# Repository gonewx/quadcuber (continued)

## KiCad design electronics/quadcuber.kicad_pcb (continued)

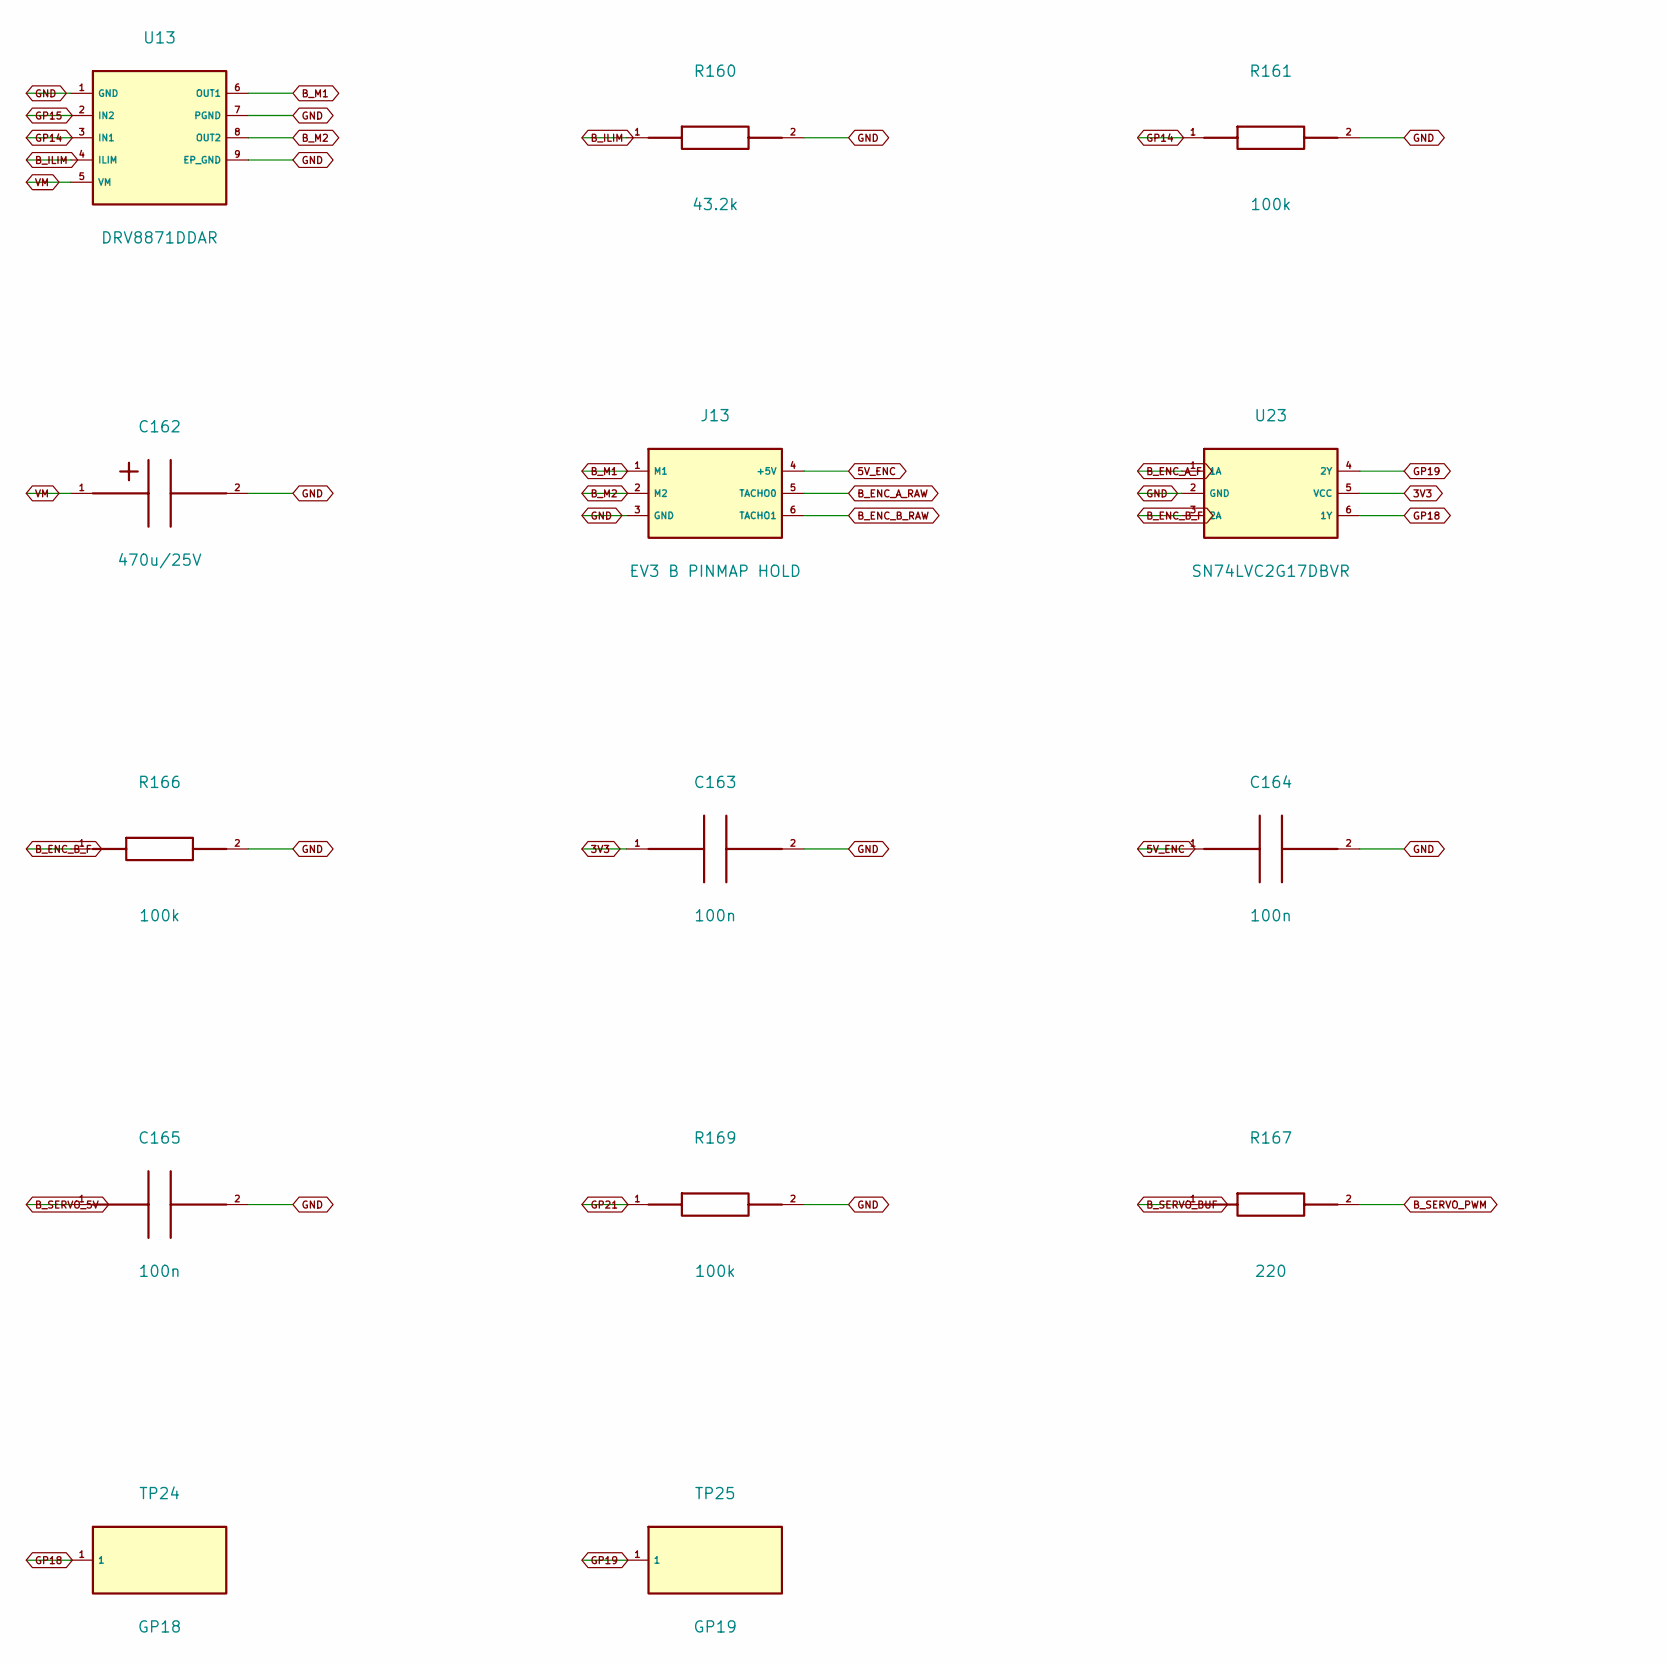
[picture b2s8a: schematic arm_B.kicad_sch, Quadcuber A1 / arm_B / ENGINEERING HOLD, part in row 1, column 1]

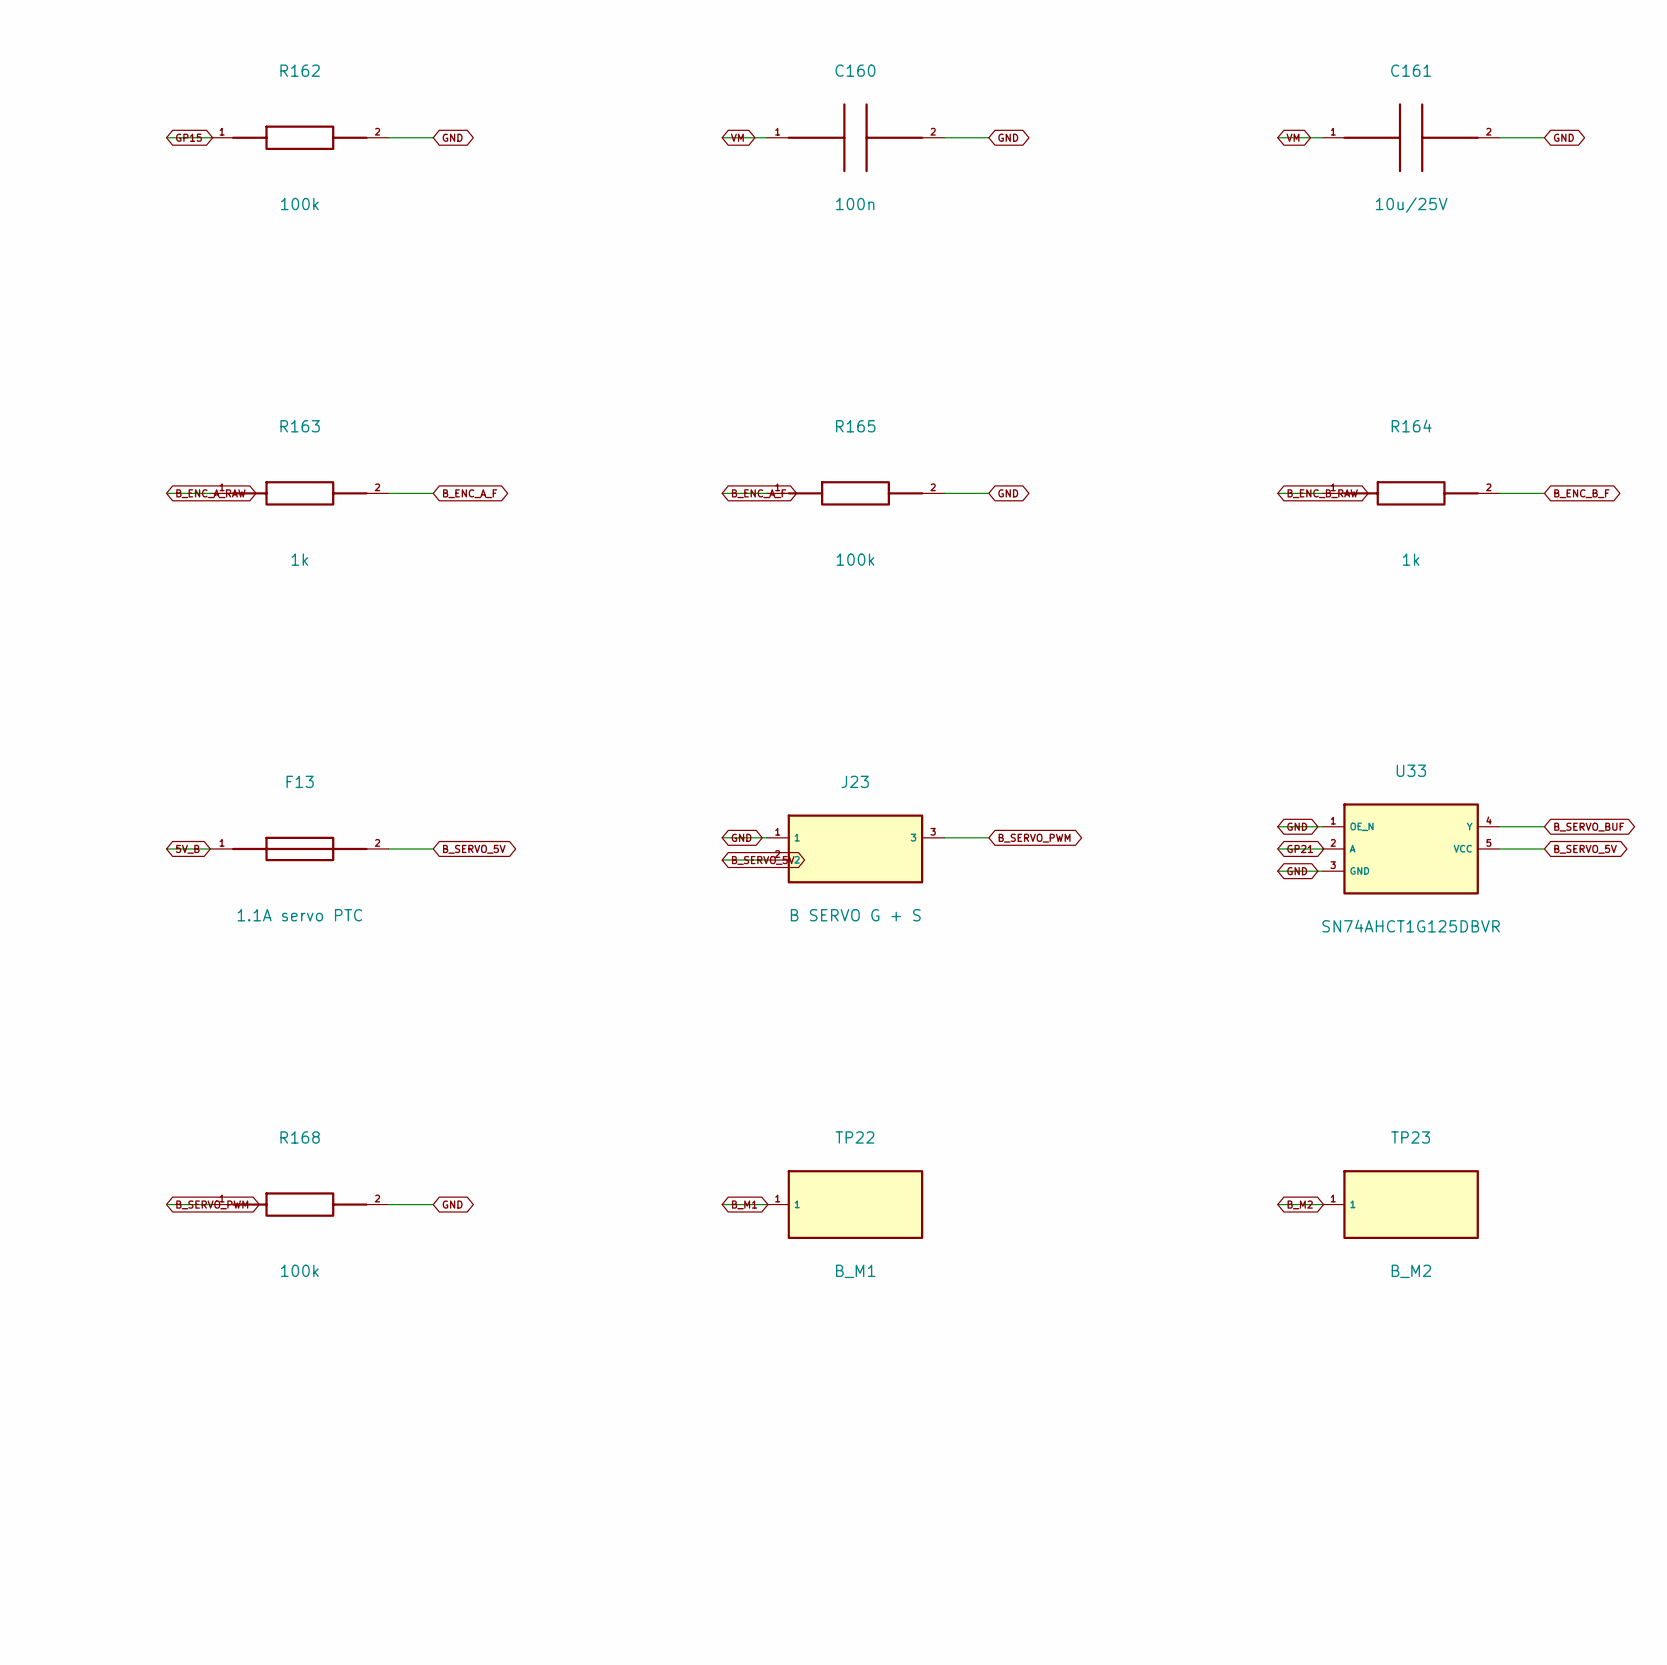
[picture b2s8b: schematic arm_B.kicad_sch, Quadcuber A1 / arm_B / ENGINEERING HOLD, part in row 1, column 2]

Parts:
C160, C163, C164, C165: 100n; C_0805_2012Metric; MPN GRM21BR71H104KA01L
C161: 10u/25V; C_1210_3225Metric; MPN GRM32DR71E106KA12L
C162: 470u/25V; CP_Radial_D10.0mm_P5.00mm; MPN EEU-FR1E471
F13: 1.1A servo PTC; Fuse_Bourns_MF_MSMF_Style2_1812; MPN MF-MSMF110/16X-2
J13: EV3 B PINMAP HOLD; EV3_UserDrawing_PINMAP_HOLD; MPN UNCONFIRMED user drawing
J23: B SERVO G + S; PinHeader_1x03_P2.54mm_Vertical; MPN 61300311121
R160: 43.2k; R_0603_1608Metric; MPN RC0603FR-0743K2L
R161, R162, R165, R166, R168, R169: 100k; R_0603_1608Metric; MPN RC0603FR-07100KL
R163, R164: 1k; R_0603_1608Metric; MPN RC0603FR-071KL
R167: 220; R_0603_1608Metric; MPN RC0603FR-07220RL
TP22: B_M1; TestPoint_Pad_D1.5mm; MPN N/A PCB copper
TP23: B_M2; TestPoint_Pad_D1.5mm; MPN N/A PCB copper
TP24: GP18; TestPoint_Pad_D1.5mm; MPN N/A PCB copper
TP25: GP19; TestPoint_Pad_D1.5mm; MPN N/A PCB copper
U13: DRV8871DDAR; Texas_HTSOP-8-1EP_3.9x4.9mm_P1.27mm_EP2.95x4.9mm_Mask2.4x3.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; MPN DRV8871DDAR
U23: SN74LVC2G17DBVR; SOT-23-6; MPN SN74LVC2G17DBVR
U33: SN74AHCT1G125DBVR; SOT-23-5; MPN SN74AHCT1G125DBVR

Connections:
3V3: C163.1, U23.5 (VCC); also elsewhere on the board
5V_B: F13.1; also elsewhere on the board
5V_ENC: C164.1, J13.4 (+5V); also elsewhere on the board
B_ENC_A_F: R163.2, R165.1, U23.1 (1A)
B_ENC_A_RAW: J13.5 (TACHO0), R163.1
B_ENC_B_F: R164.2, R166.1, U23.3 (2A)
B_ENC_B_RAW: J13.6 (TACHO1), R164.1
B_ILIM: R160.1, U13.4 (ILIM)
B_M1: J13.1 (M1), TP22.1, U13.6 (OUT1)
B_M2: J13.2 (M2), TP23.1, U13.8 (OUT2)
B_SERVO_5V: C165.1, F13.2, J23.2, U33.5 (VCC)
B_SERVO_BUF: R167.1, U33.4 (Y)
B_SERVO_PWM: J23.3, R167.2, R168.1
GND: C160.2, C161.2, C162.2 (-), C163.2, C164.2, C165.2, J13.3 (GND), J23.1, R160.2, R161.2, R162.2, R165.2, R166.2, R168.2, R169.2, U13.1 (GND), U13.7 (PGND), U13.9 (EP_GND), U23.2 (GND), U33.1 (OE_N), U33.3 (GND); also elsewhere on the board
GP14: R161.1, U13.3 (IN1); also elsewhere on the board
GP15: R162.1, U13.2 (IN2); also elsewhere on the board
GP18: TP24.1, U23.6 (1Y); also elsewhere on the board
GP19: TP25.1, U23.4 (2Y); also elsewhere on the board
GP21: R169.1, U33.2 (A); also elsewhere on the board
VM: C160.1, C161.1, C162.1 (+), U13.5 (VM); also elsewhere on the board

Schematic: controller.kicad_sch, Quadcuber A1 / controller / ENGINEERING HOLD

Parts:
C400: 100n; C_0402_1005Metric; MPN GRM155R71C104KA88D
D7: USER LED GP25; LED_0603_1608Metric; MPN LTST-C190KGKT
F2: 0.5A encoder PTC; Fuse_1812_4532Metric; MPN MF-MSMF050-2
J2: UART GND TX RX; PinHeader_1x03_P2.54mm_Vertical; MPN 61300311121
J3: RESET; PinHeader_1x02_P2.54mm_Vertical; MPN 61300211121
J4: SWD VREF D G C; PinHeader_1x04_P2.54mm_Vertical; MPN 61300411121
R400: 10k; R_0603_1608Metric; MPN RC0603FR-0710KL
R405, R406: 100k; R_0603_1608Metric; MPN RC0603FR-07100KL
R410: 1k; R_0603_1608Metric; MPN RC0603FR-071KL
S2: RUN RESET; SW_SPST_TL3342; MPN TL3342F160QG
TP1: GND; TestPoint_Pad_D2.0mm; MPN N/A PCB copper
TP2: VM; TestPoint_Pad_D2.0mm; MPN N/A PCB copper
TP3: 5V_A; TestPoint_Pad_D2.0mm; MPN N/A PCB copper
TP4: 5V_B; TestPoint_Pad_D2.0mm; MPN N/A PCB copper
TP5: 5V_ENC; TestPoint_Pad_D2.0mm; MPN N/A PCB copper
TP6: 3V3; TestPoint_Pad_D2.0mm; MPN N/A PCB copper
TP7: VSYS; TestPoint_Pad_D2.0mm; MPN N/A PCB copper
U1: RP2040; QFN-56-1EP_7x7mm_P0.4mm_EP3.2x3.2mm_ThermalVias; MPN RP2040

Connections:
1V1: U1.23 (DVDD), U1.45 (VREG_OUT), U1.50 (DVDD); also elsewhere on the board
3V3: J4.1, R400.1, TP6.1, U1.1 (IOVDD), U1.10 (IOVDD), U1.22 (IOVDD), U1.33 (IOVDD), U1.42 (IOVDD), U1.43 (ADC_AVDD), U1.44 (VREG_IN), U1.48 (USB_VDD), U1.49 (IOVDD); also elsewhere on the board
5V_A: F2.1, TP3.1; also elsewhere on the board
5V_B: TP4.1; also elsewhere on the board
5V_ENC: F2.2, TP5.1; also elsewhere on the board
GND: C400.2, D7.1 (K), J2.1, J3.2, J4.3, R406.2, S2.2, TP1.1, U1.19 (TESTEN), U1.57 (GND_EP); also elsewhere on the board
GP0: J2.2, U1.2 (GPIO0)
GP1: J2.3, U1.3 (GPIO1)
GP2: U1.4 (GPIO2); also elsewhere on the board
GP3: U1.5 (GPIO3); also elsewhere on the board
GP4: U1.6 (GPIO4); also elsewhere on the board
GP5: U1.7 (GPIO5); also elsewhere on the board
GP6: U1.8 (GPIO6); also elsewhere on the board
GP7: U1.9 (GPIO7); also elsewhere on the board
GP8: U1.11 (GPIO8); also elsewhere on the board
GP9: U1.12 (GPIO9); also elsewhere on the board
GP10: U1.13 (GPIO10); also elsewhere on the board
GP11: U1.14 (GPIO11); also elsewhere on the board
GP12: U1.15 (GPIO12); also elsewhere on the board
GP13: U1.16 (GPIO13); also elsewhere on the board
GP14: U1.17 (GPIO14); also elsewhere on the board
GP15: U1.18 (GPIO15); also elsewhere on the board
GP16: U1.27 (GPIO16); also elsewhere on the board
GP17: U1.28 (GPIO17); also elsewhere on the board
GP18: U1.29 (GPIO18); also elsewhere on the board
GP19: U1.30 (GPIO19); also elsewhere on the board
GP20: U1.31 (GPIO20); also elsewhere on the board
GP21: U1.32 (GPIO21); also elsewhere on the board
GP24: R405.2, R406.1, U1.36 (GPIO24)
GP25: R410.1, U1.37 (GPIO25)
LED_ANODE: D7.2 (A), R410.2
QSPI_SCLK: U1.52 (QSPI_SCLK); also elsewhere on the board
QSPI_SD0: U1.53 (QSPI_SD0); also elsewhere on the board
QSPI_SD1: U1.55 (QSPI_SD1); also elsewhere on the board
QSPI_SD2: U1.54 (QSPI_SD2); also elsewhere on the board
QSPI_SD3: U1.51 (QSPI_SD3); also elsewhere on the board
QSPI_SS: U1.56 (QSPI_SS); also elsewhere on the board
RUN: C400.1, J3.1, R400.2, S2.1, U1.26 (RUN)
SWCLK: J4.4, U1.24 (SWCLK)
SWDIO: J4.2, U1.25 (SWDIO)
USB_DM_MCU: U1.46 (USB_DM); also elsewhere on the board
USB_DP_MCU: U1.47 (USB_DP); also elsewhere on the board
USB_VBUS: R405.1; also elsewhere on the board
VM: TP2.1; also elsewhere on the board
VSYS: TP7.1; also elsewhere on the board
XIN: U1.20 (XIN); also elsewhere on the board
XOUT: U1.21 (XOUT); also elsewhere on the board

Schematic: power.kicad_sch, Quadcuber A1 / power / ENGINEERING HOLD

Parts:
C2, C3: 470u/25V; CP_Radial_D10.0mm_P5.00mm; MPN EEU-FR1E471
C4, C5: 100n; C_0805_2012Metric; MPN GRM21BR71H104KA01L
D3: SMBJ12A transient clamp; D_SMB; MPN SMBJ12A
D4: SMBJ12CA input transient; D_SMB; MPN SMBJ12CA
F1: 8A 24V time-lag fuse; Fuse_Littelfuse_407_1206; MPN 0407008.WR
J1: 9V DC center-positive; Jack_DC_Switchcraft_RASPC722X; MPN RASPC722X
Q1: CSD18540Q5B; TDSON-8-1; MPN CSD18540Q5B
R500, R501: 300R 1W VM bleed; R_2512_6332Metric; MPN CRCW2512300RFKEG
U4: LM74700QDBVRQ1; SOT-23-6; MPN LM74700QDBVRQ1

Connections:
GND: C2.2 (-), C3.2 (-), C5.2, D3.2 (A), D4.2, J1.2 (SLEEVE_GND), R500.2, R501.2, U4.2 (GND); also elsewhere on the board
IDEAL_GATE: Q1.4 (G), U4.5 (GATE)
IDEAL_VCAP: C4.1, U4.1 (VCAP)
VIN: F1.1, J1.1 (CENTER_9V)
VIN_FUSED: C4.2, C5.1, D4.1, F1.2, Q1.1 (S), Q1.2 (S), Q1.3 (S), U4.3 (EN), U4.6 (ANODE)
VM: C2.1 (+), C3.1 (+), D3.1 (K), Q1.5 (D_EP), R500.1, R501.1, U4.4 (CATHODE); also elsewhere on the board

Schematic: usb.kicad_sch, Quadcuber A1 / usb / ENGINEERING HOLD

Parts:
C423: 1u/16V; C_0805_2012Metric; MPN GRM21BR71C105KA01L
C427: 100n; C_0402_1005Metric; MPN GRM155R71C104KA88D
D5: SS14 USB isolation; D_SMA; MPN SS14-E3/61T
F3: 0.5A USB PTC; Fuse_1812_4532Metric; MPN MF-MSMF050-2
J5: USB-C data / BOOTSEL; USB_C_Receptacle_GCT_USB4105-xx-A_16P_TopMnt_Horizontal; MPN USB4105-GF-A
R401, R402: 5.1k; R_0603_1608Metric; MPN RC0603FR-075K1L
R403, R404: 27; R_0402_1005Metric; MPN RC0402FR-0727RL
U6: USBLC6-2SC6; SOT-23-6; MPN USBLC6-2SC6

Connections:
GND: C423.2, C427.2, J5.A1, J5.A12, J5.B1, J5.B12, J5.S1, R401.2, R402.2, U6.2 (GND); also elsewhere on the board
USB_CC1: J5.A5, R401.1
USB_CC2: J5.B5, R402.1
USB_DM: J5.A7, J5.B7, R403.1, U6.3 (IO2), U6.4 (IO2)
USB_DM_MCU: R403.2; also elsewhere on the board
USB_DP: J5.A6, J5.B6, R404.1, U6.1 (IO1), U6.6 (IO1)
USB_DP_MCU: R404.2; also elsewhere on the board
USB_FUSED: D5.2 (A), F3.2
USB_VBUS: C423.1, F3.1, J5.A4, J5.A9, J5.B4, J5.B9; also elsewhere on the board
VSYS: C427.1, D5.1 (K), U6.5 (VBUS); also elsewhere on the board

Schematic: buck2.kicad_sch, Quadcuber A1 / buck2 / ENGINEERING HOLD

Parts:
C30: 10u/25V; C_1210_3225Metric; MPN GRM32DR71E106KA12L
C31, C32: 100n; C_0805_2012Metric; MPN GRM21BR71H104KA01L
C33, C34: 22u/25V; C_1210_3225Metric; MPN GRM32ER71E226KE15L
C35: 75p; C_0603_1608Metric; MPN C0603C750J5GACTU
C36: 470u/10V; CP_Radial_D8.0mm_P3.50mm; MPN EEU-FR1A471; not fitted
L2: 10uH 9A Isat16A; L_Bourns_SRP1245A; MPN SRP1245A-100M
R31: 100k; R_0603_1608Metric; MPN RT0603BRD07100KL
R32: 13.3k; R_0603_1608Metric; MPN RT0603BRD0713K3L
R33: 511k; R_0603_1608Metric; MPN RC0603FR-07511KL
R34: 105k; R_0603_1608Metric; MPN RC0603FR-07105KL
U3: TPS54302DDCR; SOT-23-6; MPN TPS54302DDCR

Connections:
5V_B: C33.1, C34.1, C35.1, C36.1 (+), L2.2, R31.1; also elsewhere on the board
B2_BOOT: C32.1, U3.6 (BOOT)
B2_EN: R33.2, R34.1, U3.5 (EN)
B2_FB: C35.2, R31.2, R32.1, U3.4 (FB)
B2_SW: C32.2, L2.1, U3.2 (SW)
GND: C30.2, C31.2, C33.2, C34.2, C36.2 (-), R32.2, R34.2, U3.1 (GND); also elsewhere on the board
VM: C30.1, C31.1, R33.1, U3.3 (VIN); also elsewhere on the board

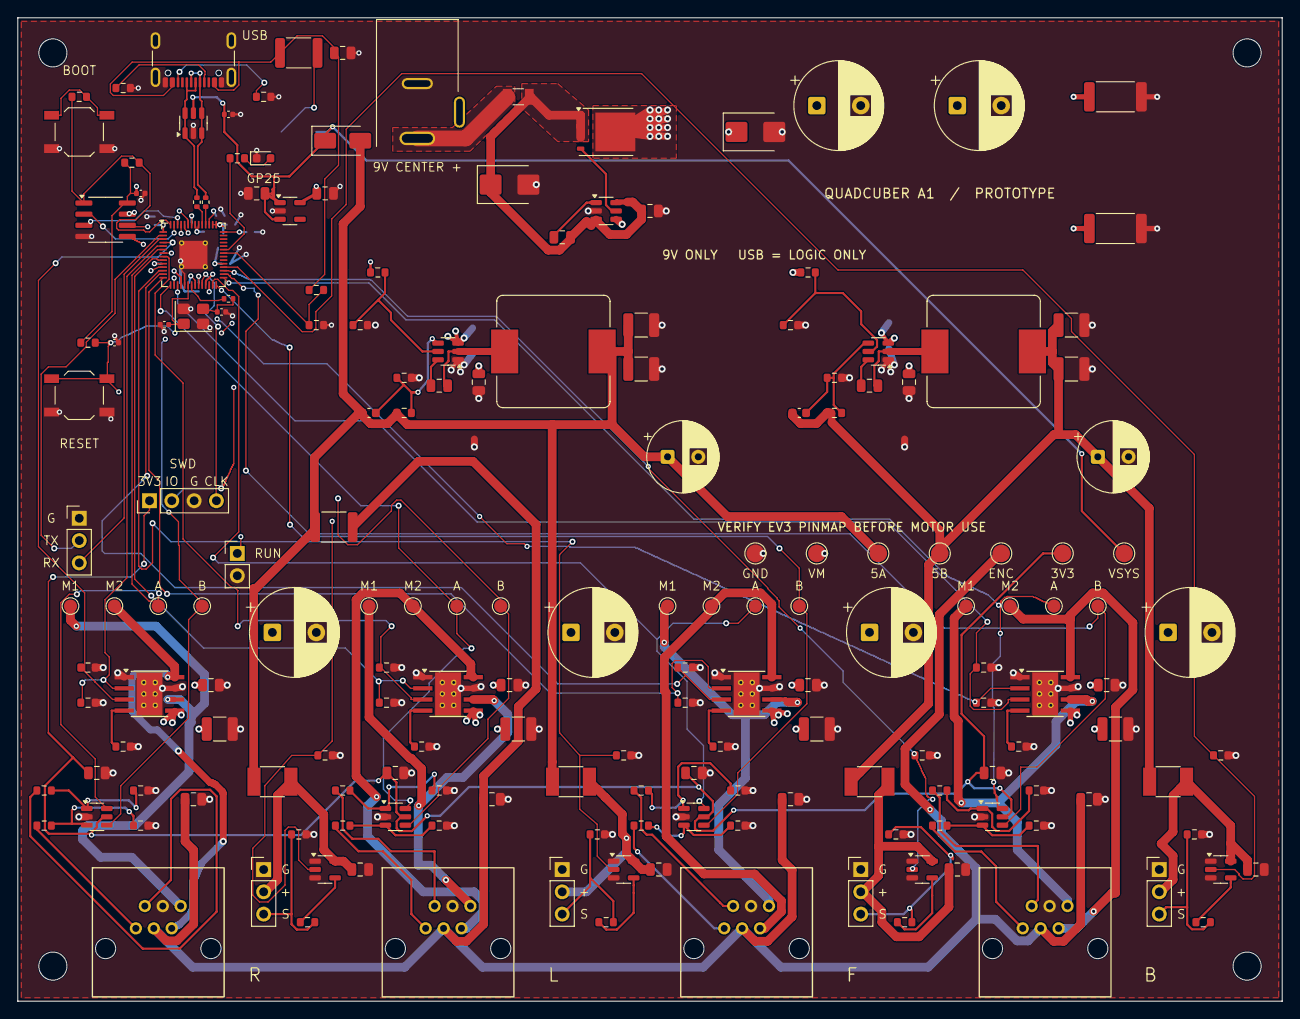
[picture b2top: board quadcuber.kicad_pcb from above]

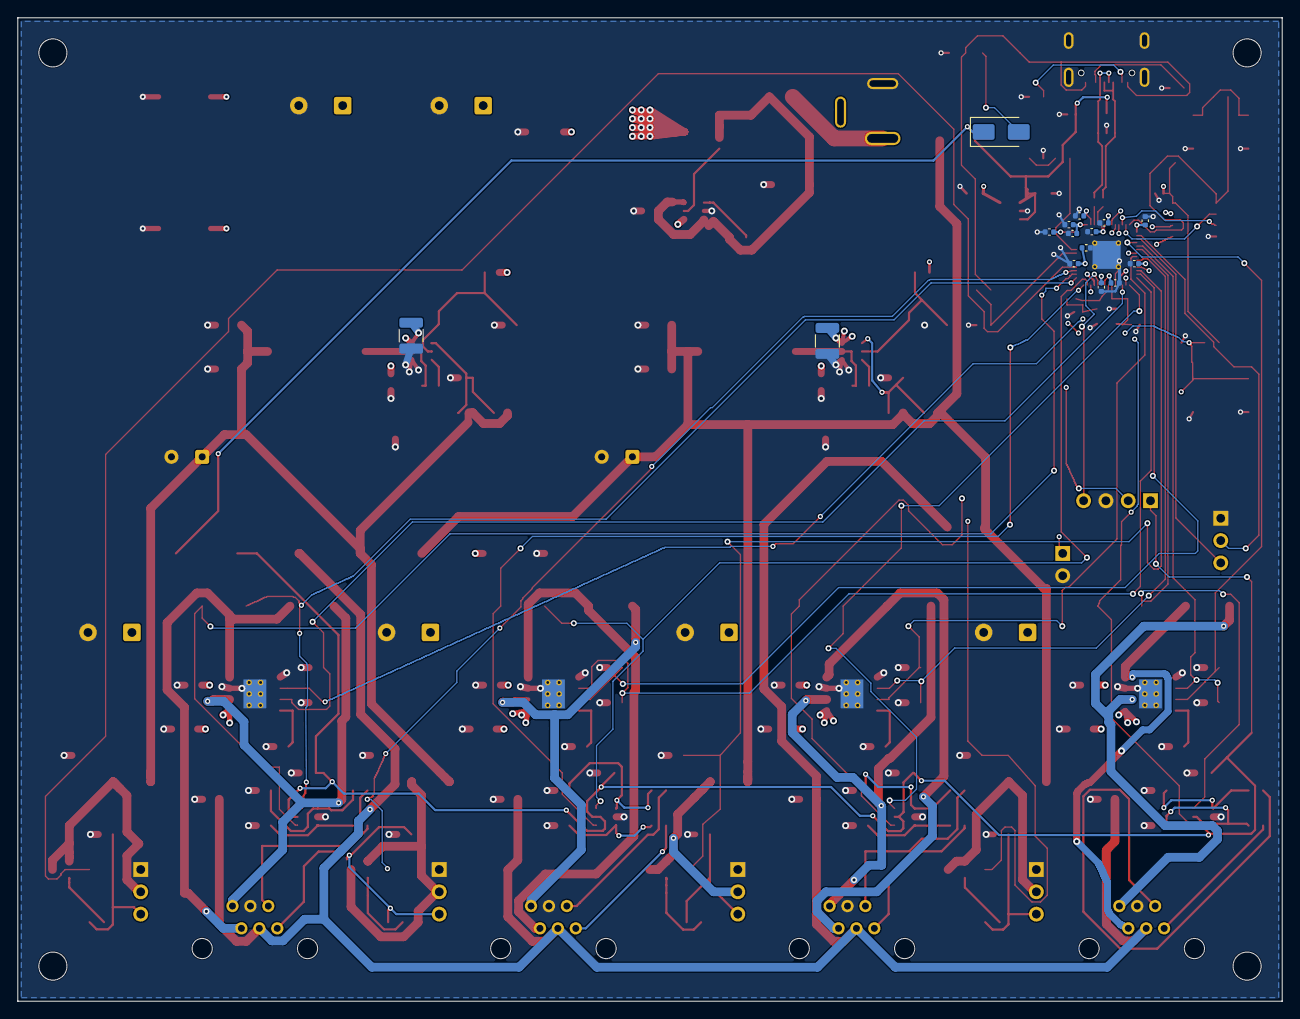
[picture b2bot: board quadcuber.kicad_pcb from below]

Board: 4 copper layers, 144.0 x 112.0 mm, 200 parts (15 on the bottom side), 106 nets.

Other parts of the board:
H1, H2, H3, H4: M3 insulated standoff; MountingHole_3.2mm_M3

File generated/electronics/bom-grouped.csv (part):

References,Value,Manufacturer,MPN,Footprint,Quantity,Notes
U1,RP2040,Raspberry Pi,RP2040,Quadcuber:QFN-56-1EP_7x7mm_P0.4mm_EP3.2x3.2mm_ThermalVias,1,"Bare RP2040, not a Pico module. EP57 and TESTEN19 ground; DVDD23/50 supplied only by VREG_OUT45."
J2,UART GND TX RX,Wurth Elektronik,61300311121,Quadcuber:PinHeader_1x03_P2.54mm_Vertical,1,
J3,RESET,Wurth Elektronik,61300211121,Quadcuber:PinHeader_1x02_P2.54mm_Vertical,1,
J4,SWD VREF D G C,Wurth Elektronik,61300411121,Quadcuber:PinHeader_1x04_P2.54mm_Vertical,1,
R400; R407,10k,Yageo,RC0603FR-0710KL,Quadcuber:R_0603_1608Metric,2,
S2,RUN RESET,E-Switch,TL3342F160QG,Quadcuber:SW_SPST_TL3342,1,
C400; C410; C411; C412; C413; C414; C415; C416; C417; C418; C419; C427; C424,100n,Murata,GRM155R71C104KA88D,Quadcuber:C_0402_1005Metric,13,
C420; C421,1u,Murata,GRM155R61C105KA12D,Quadcuber:C_0402_1005Metric,2,
D2,SS14 external logic isolation,Vishay,SS14-E3/61T,Quadcuber:D_SMA,1,
D5,SS14 USB isolation,Vishay,SS14-E3/61T,Quadcuber:D_SMA,1,
C1; C423,1u/16V,Murata,GRM21BR71C105KA01L,Quadcuber:C_0805_2012Metric,2,
U5,TLV75533PDBVR,Texas Instruments,TLV75533PDBVR,Quadcuber:SOT-23-5,1,3.3V/500mA IC rating; controller continuous design target <=150mA; no external 3V3 injection.
C422,4.7u/16V,KEMET,C0805C475K4PACTU,Quadcuber:C_0805_2012Metric,1,
J5,USB-C data / BOOTSEL,GCT,USB4105-GF-A,Quadcuber:USB_C_Receptacle_GCT_USB4105-xx-A_16P_TopMnt_Horizontal,1,USB2 device only. CC1/CC2 each 5.1k to ground. Shell ground. No PD.
R401; R402,5.1k,Yageo,RC0603FR-075K1L,Quadcuber:R_0603_1608Metric,2,
F3,0.5A USB PTC,Bourns,MF-MSMF050-2,Quadcuber:Fuse_1812_4532Metric,1,
U6,USBLC6-2SC6,STMicroelectronics,USBLC6-2SC6,Quadcuber:SOT-23-6,1,
R403; R404,27,Yageo,RC0402FR-0727RL,Quadcuber:R_0402_1005Metric,2,
R405; R406; R101; R102; R105; R106; R109; R108; R121; R122; R125; R126; R129; R128; R141; R142; R145; R146; R149; R148; R161; R162; R165; R166; R169; R168,100k,Yageo,RC0603FR-07100KL,Quadcuber:R_0603_1608Metric,26,
U7,W25Q16RVCNJQ 2MiB,Winbond,W25Q16RVCNJQ,Quadcuber:SOIC-8_3.9x4.9mm_P1.27mm,1,Current-production RV successor per Winbond PCN DM202601-03-A / AN0000070. CN 150mil SOP8; use QUADCUBER_A1 MicroPython boot2 QE-mask adaptation.
R408; R410; R103; R104; R123; R124; R143; R144; R163; R164,1k,Yageo,RC0603FR-071KL,Quadcuber:R_0603_1608Metric,10,
S1,BOOTSEL,E-Switch,TL3342F160QG,Quadcuber:SW_SPST_TL3342,1,
Y1,12MHz CL10pF,Abracon,ABM8-272-T3,Quadcuber:Crystal_SMD_3225-4Pin_3.2x2.5mm,1,
R409,1k,Yageo,RC0402FR-071KL,Quadcuber:R_0402_1005Metric,1,
C425; C426,15p,Murata,GRM1555C1H150JA01D,Quadcuber:C_0402_1005Metric,2,
D7,USER LED GP25,Lite-On,LTST-C190KGKT,Quadcuber:LED_0603_1608Metric,1,
J1,9V DC center-positive,Switchcraft,RASPC722X,Quadcuber:Jack_DC_Switchcraft_RASPC722X,1,"5.5/2.1 mm mating plug 762/762Z, 9.5 mm barrel; 5A carrying rating, regulated 9V continuous input budget <=5A. Project pins 1=center, 2=sleeve, 3=sleeve shunt NC. Drawing visually verified by parent thread; original PDF pending local archive. See sources/raspc722x-review.md."
F1,8A 24V time-lag fuse,Littelfuse,0407008.WR,Quadcuber:Fuse_Littelfuse_407_1206,1,"407 time-lag; 24VDC, 60A interrupt, nominal melting I2t24.12A2s; not fast semiconductor protection. Continuous input design budget <=5A; current-limited 9V source required."
U4,LM74700QDBVRQ1,Texas Instruments,LM74700QDBVRQ1,Quadcuber:SOT-23-6,1,Ideal diode / reverse polarity. EN is NOT a power disconnect.
Q1,CSD18540Q5B,Texas Instruments,CSD18540Q5B,Quadcuber:TDSON-8-1,1,
C4; C5; C21; C22; C31; C32; C100; C103; C104; C105; C120; C123; C124; C125; C140; C143; C144; C145; C160; C163; C164; C165,100n,Murata,GRM21BR71H104KA01L,Quadcuber:C_0805_2012Metric,22,
D4,SMBJ12CA input transient,Littelfuse,SMBJ12CA,Quadcuber:D_SMB,1,
D3,SMBJ12A transient clamp,Littelfuse,SMBJ12A,Quadcuber:D_SMB,1,"12V stand-off, 19.9V rated pulse clamp. Pulse-only; never sustained 12V input."
C2; C3; C102; C122; C142; C162,470u/25V,Panasonic,EEU-FR1E471,Quadcuber:CP_Radial_D10.0mm_P5.00mm,6,
R500; R501,300R 1W VM bleed,Vishay,CRCW2512300RFKEG,Quadcuber:R_2512_6332Metric,2,"Two 300R/1% in parallel:150R VM bleed, 0.562W total at9.18V. Operating envelope total regen <=0.05J/event and <=5Hz; verify actual energy and resistor film temperature. Not a full-power brake."
U2; U3,TPS54302DDCR,Texas Instruments,TPS54302DDCR,Quadcuber:SOT-23-6,2,
C20; C30; C101; C121; C141; C161,10u/25V,Murata,GRM32DR71E106KA12L,Quadcuber:C_1210_3225Metric,6,
L1; L2,10uH 9A Isat16A,Bourns,SRP1245A-100M,Quadcuber:L_Bourns_SRP1245A,2,
C23; C24; C33; C34,22u/25V,Murata,GRM32ER71E226KE15L,Quadcuber:C_1210_3225Metric,4,
R21; R31,100k,Yageo,RT0603BRD07100KL,Quadcuber:R_0603_1608Metric,2,
R22; R32,13.3k,Yageo,RT0603BRD0713K3L,Quadcuber:R_0603_1608Metric,2,
C25; C35,75p,KEMET,C0603C750J5GACTU,Quadcuber:C_0603_1608Metric,2,
R23; R33,511k,Yageo,RC0603FR-07511KL,Quadcuber:R_0603_1608Metric,2,
R24; R34,105k,Yageo,RC0603FR-07105KL,Quadcuber:R_0603_1608Metric,2,
C26; C36,470u/10V,Panasonic,EEU-FR1A471,Quadcuber:CP_Radial_D8.0mm_P3.50mm,0,DNP by default. Populate only after loop/step-response verification with added 470uF.
F2,0.5A encoder PTC,Bourns,MF-MSMF050-2,Quadcuber:Fuse_1812_4532Metric,1,
U10; U11; U12; U13,DRV8871DDAR,Texas Instruments,DRV8871DDAR,Quadcuber:Texas_HTSOP-8-1EP_3.9x4.9mm_P1.27mm_EP2.95x4.9mm_Mask2.4x3.1mm_ThermalVias,4,
R100; R120; R140; R160,43.2k,Yageo,RC0603FR-0743K2L,Quadcuber:R_0603_1608Metric,4,
J10,EV3 R PINMAP HOLD,Unconfirmed (Coorle watermark),UNCONFIRMED user drawing,Quadcuber:EV3_UserDrawing_PINMAP_HOLD,1,"Nominal hole geometry from user drawing. HOLD: actual MPN, numbering 1-5, observation side, contact current and ear envelope require confirmation. See sources/ev3-user-drawing-review.md."
U20; U21; U22; U23,SN74LVC2G17DBVR,Texas Instruments,SN74LVC2G17DBVR,Quadcuber:SOT-23-6,4,
F10; F11; F12; F13,1.1A servo PTC,Bourns,MF-MSMF110/16X-2,Quadcuber:Fuse_Bourns_MF_MSMF_Style2_1812,4,
J20,R SERVO G + S,Wurth Elektronik,61300311121,Quadcuber:PinHeader_1x03_P2.54mm_Vertical,1,
U30; U31; U32; U33,SN74AHCT1G125DBVR,Texas Instruments,SN74AHCT1G125DBVR,Quadcuber:SOT-23-5,4,Input leakage specified at VCC=0; prevents USB-only GPIO phantom servo supply.
R107; R127; R147; R167,220,Yageo,RC0603FR-07220RL,Quadcuber:R_0603_1608Metric,4,
J11,EV3 L PINMAP HOLD,Unconfirmed (Coorle watermark),UNCONFIRMED user drawing,Quadcuber:EV3_UserDrawing_PINMAP_HOLD,1,"Nominal hole geometry from user drawing. HOLD: actual MPN, numbering 1-5, observation side, contact current and ear envelope require confirmation. See sources/ev3-user-drawing-review.md."
J21,L SERVO G + S,Wurth Elektronik,61300311121,Quadcuber:PinHeader_1x03_P2.54mm_Vertical,1,
J12,EV3 F PINMAP HOLD,Unconfirmed (Coorle watermark),UNCONFIRMED user drawing,Quadcuber:EV3_UserDrawing_PINMAP_HOLD,1,"Nominal hole geometry from user drawing. HOLD: actual MPN, numbering 1-5, observation side, contact current and ear envelope require confirmation. See sources/ev3-user-drawing-review.md."
J22,F SERVO G + S,Wurth Elektronik,61300311121,Quadcuber:PinHeader_1x03_P2.54mm_Vertical,1,
J13,EV3 B PINMAP HOLD,Unconfirmed (Coorle watermark),UNCONFIRMED user drawing,Quadcuber:EV3_UserDrawing_PINMAP_HOLD,1,"Nominal hole geometry from user drawing. HOLD: actual MPN, numbering 1-5, observation side, contact current and ear envelope require confirmation. See sources/ev3-user-drawing-review.md."
J23,B SERVO G + S,Wurth Elektronik,61300311121,Quadcuber:PinHeader_1x03_P2.54mm_Vertical,1,
TP1,GND,PCB,N/A PCB copper,Quadcuber:TestPoint_Pad_D2.0mm,0,
TP2,VM,PCB,N/A PCB copper,Quadcuber:TestPoint_Pad_D2.0mm,0,
TP3,5V_A,PCB,N/A PCB copper,Quadcuber:TestPoint_Pad_D2.0mm,0,
TP4,5V_B,PCB,N/A PCB copper,Quadcuber:TestPoint_Pad_D2.0mm,0,
TP5,5V_ENC,PCB,N/A PCB copper,Quadcuber:TestPoint_Pad_D2.0mm,0,
TP6,3V3,PCB,N/A PCB copper,Quadcuber:TestPoint_Pad_D2.0mm,0,
TP7,VSYS,PCB,N/A PCB copper,Quadcuber:TestPoint_Pad_D2.0mm,0,
TP10,R_M1,PCB,N/A PCB copper,Quadcuber:TestPoint_Pad_D1.5mm,0,
TP11,R_M2,PCB,N/A PCB copper,Quadcuber:TestPoint_Pad_D1.5mm,0,
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
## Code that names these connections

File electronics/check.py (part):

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    check(f'U{30+i}',2,f'GP{servo[0]}');check(f'U{30+i}',5,arm+'_SERVO_5V')
    check(f'J{20+i}',1,'GND');check(f'J{20+i}',2,arm+'_SERVO_5V');check(f'J{20+i}',3,arm+'_SERVO_PWM')
# Exact protection-part check; ERC cannot detect nonexistent MPNs or wrong lands.
for ref,pins in {'F1':{1:'VIN',2:'VIN_FUSED'},'R500':{1:'VM',2:'GND'},'R501':{1:'VM',2:'GND'}}.items():
    for pin,net in pins.items():check(ref,pin,net)
verified_mpn={'F1':'0407008.WR','R500':'CRCW2512300RFKEG','R501':'CRCW2512300RFKEG'}
verified_mpn['U7']='W25Q16RVCNJQ'
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for pin in [1,10,22,33,42,43,44,48,49]:check('U1',pin,'3V3')
for pin in [23,45,50]:check('U1',pin,'1V1')
for pin in [19,57]:check('U1',pin,'GND')
for pin,net in {20:'XIN',21:'XOUT',24:'SWCLK',25:'SWDIO',26:'RUN',46:'USB_DM_MCU',47:'USB_DP_MCU',51:'QSPI_SD3',52:'QSPI_SCLK',53:'QSPI_SD0',54:'QSPI_SD2',55:'QSPI_SD1',56:'QSPI_SS'}.items():check('U1',pin,net)
for ref,pp in {
 'U7':{1:'QSPI_SS',2:'QSPI_SD1',3:'QSPI_SD2',4:'GND',5:'QSPI_SD0',6:'QSPI_SCLK',7:'QSPI_SD3',8:'3V3'},
 'U5':{1:'VSYS',2:'GND',3:'VSYS',5:'3V3'},
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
